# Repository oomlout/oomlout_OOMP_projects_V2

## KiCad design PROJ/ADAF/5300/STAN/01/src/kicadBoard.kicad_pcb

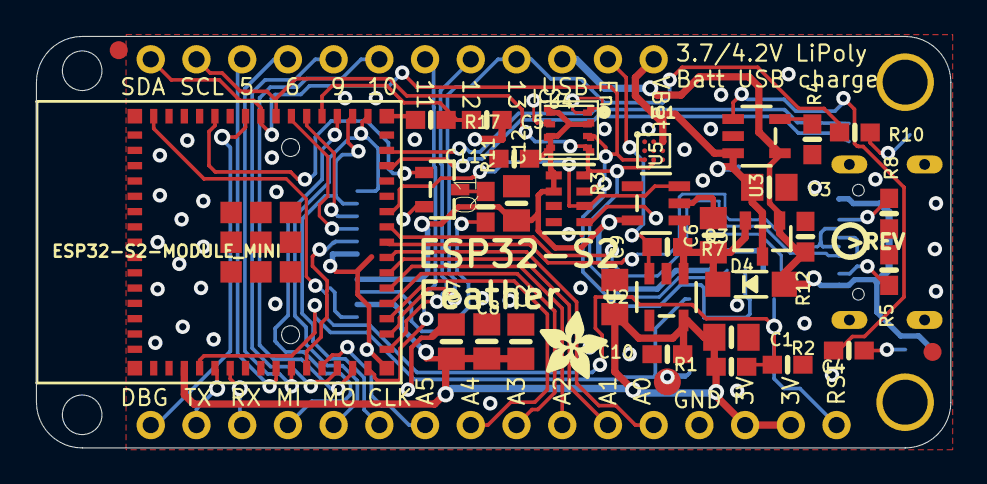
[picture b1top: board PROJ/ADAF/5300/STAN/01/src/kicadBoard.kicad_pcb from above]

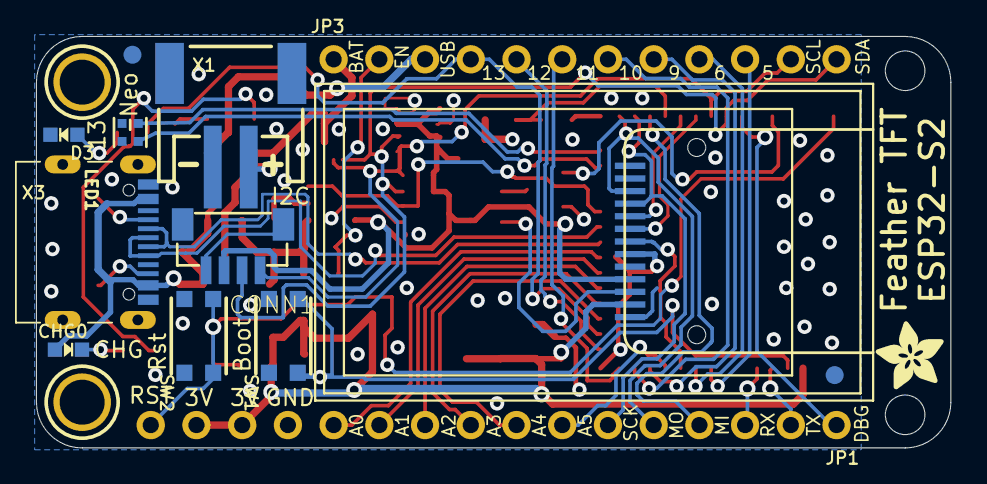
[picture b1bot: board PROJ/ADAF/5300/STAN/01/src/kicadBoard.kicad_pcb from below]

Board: 2 copper layers, 50.8 x 22.9 mm, 56 parts (16 on the bottom side), 48 nets.

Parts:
@HOLE0, @HOLE1: (no value)
C1, C2, C7, C9, C12: 10uF; 0805-NO
C3, C6, C8: 10µF; 0805-NO
C4, C5, C10, C11: 1uF; 0603-NO
CHG0: ORANGE; CHIPLED_0603_NOOUTLINE
CONN1: STEMMA_I2C_QTRA; JST_SH4_RA
D3: RED; CHIPLED_0603_NOOUTLINE
D4: MBR540; SOD-123
DISP1: DISP_LCD_GENERIC_SPI_1.14IN_240X135_WRAPUNDER; TFT_1.14IN_240X135_WRAPUNDER
IC1: LC709203F/MH; WLCSP9
IC2: BME680
JP1: 1X16_ROUND_MIN
JP3: 1X12_ROUND_MIN
LED1: WS2812B_SK6805_1515; SK6805_1515
Q1: BSS138; SOT23-R
Q3: DMG3415U; SOT23-R
R1, R2, R4, R5, R8, R10: 5.1K; 0603-NO
R3: 10K; RESPACK_4X0603
R7, R12: 100K; 0603-NO
R11: 22; 0603-NO
R17: 1Meg; 0603-NO
SW1, SW2: KMR2; BTN_KMR2_4.6X2.8
TP1: TESTPOINT_ROUND_1.5MM_NO
U1: ESP32-S2-MODULE_MINI; QFN60_ESP32-S2-MINI-1_EXP
U2, U5: AP2112-3.3; SOT23-5
U3: MCP73831T-2ACI/OT; SOT23-5
U4: BME280
U$7: PCBFEAT-REV-040
U$9, U$54: ADAFRUIT_3.5MM
U$31, U$32: MOUNTINGHOLE2.5; MOUNTINGHOLE_2.5_PLATED
U$34, U$35, U$55, U$56: FIDUCIAL_1MM
X1: JSTPH; JSTPH2_BATT
X3: USB C; USB_C_CUSB31-CFM2AX-01-X

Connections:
3.3V: C1.1, C2.1, C7.1, C8.1, C9.1, C10.1, DISP1.12, JP1.14, JP1.15, R1.2, U1.3, U2.5
A0: JP1.12, U1.22
A1: JP1.11, U1.21
A2: JP1.10, U1.20
A3: JP1.9, U1.19
A4: JP1.8, U1.18
A5: JP1.7, U1.12
BACKLITE: Q1.1, U1.41
BOOT0: SW1.B, SW1.B', TP1.P$1, U1.4
D5: JP3.10, U1.9
D6: JP3.9, U1.10
D9: JP3.8, U1.13
D10: JP3.7, U1.14
D11: JP3.6, U1.15
D12: JP3.5, U1.16
D13: JP3.4, R10.1, U1.17
D+: U1.24, X3.A6, X3.B6
D-: U1.23, X3.A7, X3.B7
EN: JP3.2, R7.1, U2.3
GND: C1.2, C2.2, C3.2, C4.2, C5.2, C6.2, C7.2, C8.2, C9.2, C10.2, C11.2, C12.2, CONN1.1, CONN1.MT1, CONN1.MT2, D3.C, DISP1.8, DISP1.13, IC1.A1, IC1.B1, IC2.1, IC2.7, JP1.13, LED1.4, Q1.2, R3.3, R3.4, R3.5, R4.1, R5.1, R8.1, R12.1, R17.1, SW1.A, SW1.A', SW2.A, SW2.A', U1.1, U1.2, U1.30, U1.42, U1.43, U1.46, U1.47, U1.48, U1.49, U1.50, U1.51, U1.52, U1.53, U1.54, U1.55, U1.56, U1.57, U1.58, U1.59, U1.60, U1.61, U1.62, U1.63, U1.64, U1.65, U1.66, U1.67, U1.68, U1.69, U1.70, U1.71, U1.72, U1.73, U2.2, U3.2, U4.1, U4.7, U5.2, X1.1, X1.NC1, X1.NC2, X3.A1B12, X3.B1A12
I2C_PWR: R3.6, U1.25, U5.3
IO38_DBLTAP: C5.1, R17.2, U1.34
LEDK: DISP1.11, R11.1
MISO: JP1.4, U1.33
MOSI: DISP1.3, JP1.5, U1.31
unnamed: CHG0.C, R2.1
unnamed: Q1.3, R11.2
unnamed: R2.2, U3.1
unnamed: R4.2, U3.5
unnamed: D3.A, R10.2
unnamed: R8.2, X3.A5
unnamed: R5.2, X3.B5
NEOPIX: LED1.1, U1.28
NEOPIX_PWR: LED1.2, U1.29
RESET: C4.1, JP1.16, R1.1, SW2.B, SW2.B', U1.45
RX: JP1.3, U1.6
SCK: DISP1.4, JP1.6, U1.32
SCL: CONN1.4, IC1.C2, IC2.4, JP3.11, R3.8, U1.37, U4.4
SDA: CONN1.3, IC1.C1, IC2.3, JP3.12, R3.7, U1.38, U4.3
TFT_CS: DISP1.7, U1.11
TFT_DC: DISP1.5, U1.35
TFT_RST: DISP1.6, U1.36
TX: JP1.2, U1.5
TXD0: JP1.1, U1.39
VBAT: C3.1, IC1.A3, JP3.1, Q3.3, U3.3, X1.2
VBUS: CHG0.A, D4.A, JP3.3, Q3.1, R12.2, U3.4, X3.A4B9, X3.B4A9
VHI: C6.1, D4.C, Q3.2, R7.2, U2.1, U5.1
VSENSOR: C11.1, C12.1, CONN1.2, DISP1.10, IC2.2, IC2.5, IC2.6, IC2.8, R3.1, R3.2, U4.2, U4.5, U4.6, U4.8, U5.5

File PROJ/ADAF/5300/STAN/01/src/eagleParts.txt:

Partlist

Exported from boardEagle.brd at 08/08/2022 07:50

EAGLE Version 9.6.2 Copyright (c) 1988-2020 Autodesk, Inc.

Assembly variant: 

Part     Value                                         Package                      Library              Position (inch)       Orientation

C1       10uF                                          0805-NO                      microbuilder         (1.52 0.242)          R0
C2       10uF                                          0805-NO                      microbuilder         (1.0595 0.2325)       R90
C3       10µF                                          0805-NO                      microbuilder         (1.603 0.57)          R0
C4       1uF                                           0603-NO                      microbuilder         (1.643 0.182)         R0
C5       1uF                                           0603-NO                      microbuilder         (0.985 0.7175)        R0
C6       10µF                                          0805-NO                      microbuilder         (1.4804252 0.46519685) R90
C7       10uF                                          0805-NO                      microbuilder         (0.9075 0.2325)       R90
C8       10µF                                          0805-NO                      microbuilder         (0.98490945 0.2328622) R90
C9       10uF                                          0805-NO                      microbuilder         (1.265 0.33)          R90
C10      1uF                                           0603-NO                      microbuilder         (1.38 0.205)          R180
C11      1uF                                           0603-NO                      microbuilder         (1.045 0.6325)        R180
C12      10uF                                          0805-NO                      microbuilder         (1.05 0.535)          R90
CHG      ORANGE                                        CHIPLED_0603_NOOUTLINE       microbuilder         (1.93 0.215)          MR270
CONN1    STEMMA_I2C_QTRA                               JST_SH4_RA                   microbuilder         (1.57 0.455)          MR180
D3       RED                                           CHIPLED_0603_NOOUTLINE       microbuilder         (1.94 0.685)          MR90
D4       MBR540                                        SOD-123                      microbuilder         (1.563 0.358)         R0
DISP1    DISP_LCD_GENERIC_SPI_1.14IN_240X135_WRAPUNDER TFT_1.14IN_240X135_WRAPUNDER adafruit_display     (0.17 0.45)           MR90
IC1      LC709203F/MH                                  WLCSP9                       adafruit_sensor      (1.35 0.65)           R0
IC2      BME680                                        BME680                       adafruit_sensor      (1.165 0.695)         R0
JP1                                                    1X16_ROUND_MIN               microbuilder         (1 0.05)              MR180
JP3                                                    1X12_ROUND_MIN               microbuilder         (0.8 0.85)            MR0
LED1     WS2812B_SK6805_1515                           SK6805_1515                  microbuilder         (1.795 0.69)          MR90
Q1       BSS138                                        SOT23-R                      microbuilder         (0.8875 0.565)        R270
Q3       DMG3415U                                      SOT23-R                      microbuilder         (1.588 0.458)         R180
R1       5.1K                                          0603-NO                      microbuilder         (1.52 0.1775)         R180
R2       5.1K                                          0603-NO                      microbuilder         (1.777 0.213)         R180
R3       10K                                           RESPACK_4X0603               microbuilder         (1.165 0.545)         R270
R4       5.1K                                          0603-NO                      microbuilder         (1.697 0.675)         R90
R5       5.1K                                          0603-NO                      microbuilder         (1.865 0.389)         R270
R7       100K                                          0603-NO                      microbuilder         (1.38 0.4395)         R0
R8       5.1K                                          0603-NO                      microbuilder         (1.865 0.5125)        R90
R10      5.1K                                          0603-NO                      microbuilder         (1.79 0.69)           R0
R11      22                                            0603-NO                      microbuilder         (0.9825 0.5275)       R90
R12      100K                                          0603-NO                      microbuilder         (1.682 0.462)         R270
R17      1Meg                                          0603-NO                      microbuilder         (0.8625 0.7175)       R0
SW1      KMR2                                          BTN_KMR2_4.6X2.8             microbuilder         (1.46 0.245)          MR90
SW2      KMR2                                          BTN_KMR2_4.6X2.8             microbuilder         (1.645 0.245)         MR90
TP1                                                    TESTPOINT_ROUND_1.5MM_NO     microbuilder         (1.38 0.1445)         R180
U$31     MOUNTINGHOLE2.5                               MOUNTINGHOLE_2.5_PLATED      microbuilder         (1.9 0.8)             MR270
U$32     MOUNTINGHOLE2.5                               MOUNTINGHOLE_2.5_PLATED      microbuilder         (1.9 0.1)             MR270
U$34     FIDUCIAL_1MM                                  FIDUCIAL_1MM                 microbuilder         (1.79 0.86)           MR270
U$35     FIDUCIAL_1MM                                  FIDUCIAL_1MM                 microbuilder         (0.25414173 0.15927559) MR270
U$55     FIDUCIAL_1MM                                  FIDUCIAL_1MM                 microbuilder         (1.96 0.21)           R0
U$56     FIDUCIAL_1MM                                  FIDUCIAL_1MM                 microbuilder         (0.18 0.87)           R0
U1       ESP32-S2-MODULE_MINI                          QFN60_ESP32-S2-MINI-1_EXP    adafruit_wireless    (0.4 0.45)            R90
U2       AP2112-3.3                                    SOT23-5                      microbuilder         (1.378 0.33)          R180
U3       MCP73831T-2ACI/OT                             SOT23-5                      microbuilder         (1.575 0.682)         R270
U4       BME280                                        BME280                       adafruit_sensor      (1.165 0.695)         R0
U5       AP2112-3.3                                    SOT23-5                      microbuilder         (1.355 0.535)         R90
X1       JSTPH                                         JSTPH2_BATT                  adafruit_electromech (1.575 0.76)          MR0
X3       USB C                                         USB_C_CUSB31-CFM2AX-01-X     adafruit_connector   (1.895 0.45)          MR270

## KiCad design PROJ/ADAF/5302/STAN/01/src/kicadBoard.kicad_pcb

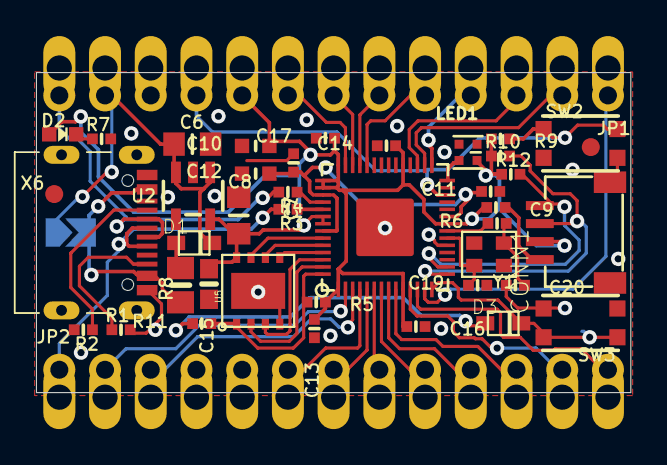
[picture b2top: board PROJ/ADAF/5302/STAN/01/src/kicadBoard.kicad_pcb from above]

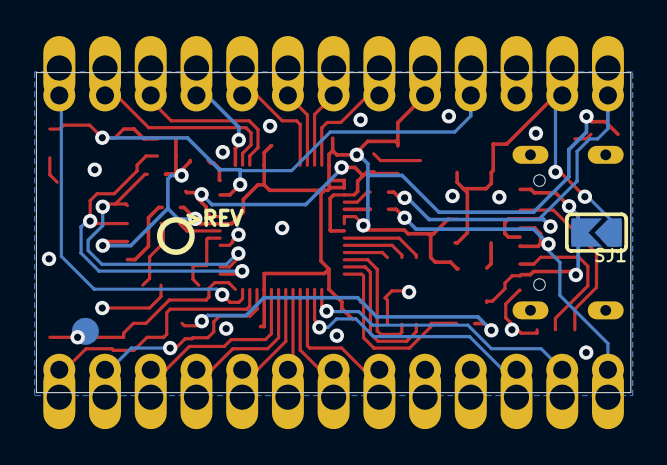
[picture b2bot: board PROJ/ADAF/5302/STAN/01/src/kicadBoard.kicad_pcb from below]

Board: 4 copper layers, 33.0 x 17.8 mm, 47 parts (4 on the bottom side), 46 nets.

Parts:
C6, C8: 10µF; _0805MP
C7, C9, C11, C13, C14, C16, C17: 0.1uF; _0402NO
C10, C12: 1uF; _0603MP
C15: 1uF; 0603-NO
C19, C20: 22pF; _0402NO
CONN1: STEMMA_I2C_QTSKINNY; JST_SH4_SKINNY
D1, D3: NSR0320; SOD-323F
D2: GREEN; CHIPLED_0603_NOOUTLINE
IC2: RP2040_QFN56; QFN56_7MM_REDUCEDEPAD
JP1, JP2: 1X13_CASTEL
LED1: WS2812B_SK6805_1515; SK6805_1515
R1, R2, R10, R12: 5.1K; _0402NO
R3, R4: 27; _0402NO
R5, R7, R9: 10K; _0402NO
R6, R11: 1K; _0402NO
R8: FUSE; 0805-NO
SJ1: SOLDERJUMPER_ARROW_NOPASTE
SW2, SW3: KMR2; BTN_KMR2_4.6X2.8
TP1: TESTPOINT_ROUND_1.5MM_NO
U2: AP2112K-3.3; SOT23-5
U5: 8MB QSPI Flash; USON8_4X4
U$17: KB2040_BOT
U$19: KB2040_TOP
U$20: PCBFEAT-REV-040
U$34, U$35: FIDUCIAL_1MM
X6: USB TYPE C; USB_C_CUSB31-CFM2AX-01-X
Y1: 12MHZ; CRYSTAL_2.5X2

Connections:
1.2V: C7.2, C11.2, C12.1, IC2.23, IC2.45, IC2.50
3.3V: C8.1, C9.1, C10.1, C13.1, C14.1, C15.1, C16.1, C17.1, CONN1.2, D2.A, IC2.1, IC2.10, IC2.22, IC2.33, IC2.42, IC2.43, IC2.44, IC2.48, IC2.49, JP1.9, JP1.9C, LED1.2, R5.2, R9.1, R10.1, R12.1, U2.5, U5.8
A0: IC2.38, JP1.5, JP1.5C
A1: IC2.39, JP1.6, JP1.6C
A2: IC2.40, JP1.7, JP1.7C
A3: IC2.41, JP1.8, JP1.8C
CC1: R2.1, X6.A5
CC2: R1.1, X6.B5
D0: IC2.2, JP2.2, JP2.2C
D1: IC2.3, JP2.3, JP2.3C
D2: IC2.4, JP2.6, JP2.6C
D3: IC2.5, JP2.7, JP2.7C
D4: IC2.6, JP2.8, JP2.8C
D5: IC2.7, JP2.9, JP2.9C
D6: IC2.8, JP2.10, JP2.10C
D7: IC2.9, JP2.11, JP2.11C
D8: IC2.11, JP2.12, JP2.12C
D9: IC2.12, JP2.13, JP2.13C
D10: IC2.13, JP1.1, JP1.1C
D+: JP2.1, JP2.1C, R3.2, X6.A6, X6.B6
D-: JP1.13, JP1.13C, R4.2, X6.A7, X6.B7
GND: C6.2, C7.1, C8.2, C9.2, C10.2, C11.1, C12.2, C13.2, C14.2, C15.2, C16.2, C17.2, C19.1, C20.1, CONN1.1, CONN1.MT1, CONN1.MT2, IC2.19, IC2.P$1, JP1.11, JP1.11C, JP2.4, JP2.4C, JP2.5, JP2.5C, LED1.4, R1.2, R2.2, R7.2, SW2.B, SW2.B', SW3.B, SW3.B', U2.2, U5.4, U5.PAD, X6.A1B12, X6.B1A12
MISO: IC2.31, JP1.3, JP1.3C
MOSI: IC2.30, JP1.2, JP1.2C
unnamed: IC2.47, R3.1
unnamed: D2.C, R7.1
unnamed: IC2.46, R4.1
unnamed: D3.A, R11.2
unnamed: C19.2, IC2.20, Y1.3
unnamed: C20.2, R6.1, Y1.1
unnamed: IC2.21, R6.2
unnamed: D1.A, R8.2
NEOPIX: IC2.28, LED1.1
QSPI_CS: IC2.56, R5.1, R11.1, U5.1
QSPI_DATA[0]: IC2.53, U5.5
QSPI_DATA[1]: IC2.55, U5.2
QSPI_DATA[2]: IC2.54, U5.3
QSPI_DATA[3]: IC2.51, U5.7
QSPI_SCK: IC2.52, U5.6
RAW: C6.1, D1.C, JP1.12, JP1.12C, SJ1.1, U2.1, U2.3
SCL: CONN1.4, IC2.16, R12.2
SCLK: IC2.29, JP1.4, JP1.4C
SDA: CONN1.3, IC2.15, R10.2
USBBOOT: D3.C, IC2.14, SW3.A, SW3.A', TP1.P$1
VBUS: R8.1, SJ1.2, X6.A4B9, X6.B4A9
~RESET: IC2.26, JP1.10, JP1.10C, R9.2, SW2.A, SW2.A'

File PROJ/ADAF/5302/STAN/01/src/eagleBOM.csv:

"Part";"Value";"Device";"Package";"Description";"BOM";"REV";
"C6";"10µF";"CAP_CERAMIC_0805MP";"_0805MP";"Ceramic Capacitors";"";"";
"C7";"0.1uF";"CAP_CERAMIC_0402NO";"_0402NO";"Ceramic Capacitors";"";"";
"C8";"10µF";"CAP_CERAMIC_0805MP";"_0805MP";"Ceramic Capacitors";"";"B";
"C9";"0.1uF";"CAP_CERAMIC_0402NO";"_0402NO";"Ceramic Capacitors";"";"";
"C10";"1uF";"CAP_CERAMIC_0603MP";"_0603MP";"Ceramic Capacitors";"";"";
"C11";"0.1uF";"CAP_CERAMIC_0402NO";"_0402NO";"Ceramic Capacitors";"";"";
"C12";"1uF";"CAP_CERAMIC_0603MP";"_0603MP";"Ceramic Capacitors";"";"";
"C13";"0.1uF";"CAP_CERAMIC_0402NO";"_0402NO";"Ceramic Capacitors";"";"";
"C14";"0.1uF";"CAP_CERAMIC_0402NO";"_0402NO";"Ceramic Capacitors";"";"";
"C15";"1uF";"CAP_CERAMIC0603_NO";"0603-NO";"Ceramic Capacitors";"";"";
"C16";"0.1uF";"CAP_CERAMIC_0402NO";"_0402NO";"Ceramic Capacitors";"";"";
"C17";"0.1uF";"CAP_CERAMIC_0402NO";"_0402NO";"Ceramic Capacitors";"";"";
"C19";"22pF";"CAP_CERAMIC_0402NO";"_0402NO";"Ceramic Capacitors";"";"";
"C20";"22pF";"CAP_CERAMIC_0402NO";"_0402NO";"Ceramic Capacitors";"";"";
"CONN1";"STEMMA_I2C_QTSKINNY";"STEMMA_I2C_QTSKINNY";"JST_SH4_SKINNY";"";"";"";
"D1";"NSR0320";"DIODESOD-323F";"SOD-323F";"Diode";"";"";
"D2";"GREEN";"LED0603_NOOUTLINE";"CHIPLED_0603_NOOUTLINE";"LED";"";"";
"D3";"NSR0320";"DIODESOD-323F";"SOD-323F";"Diode";"";"";
"IC2";"RP2040_QFN56";"RP2040_QFN56";"QFN56_7MM_REDUCEDEPAD";"";"";"";
"JP1";"";"HEADER-1X13_CASTEL";"1X13_CASTEL";"";"";"";
"JP2";"";"HEADER-1X13_CASTEL";"1X13_CASTEL";"";"";"";
"LED1";"WS2812B_SK6805_1515";"WS2812B_SK6805_1515";"SK6805_1515";"";"";"";
"R1";"5.1K";"RESISTOR_0402NO";"_0402NO";"Resistors";"";"";
"R2";"5.1K";"RESISTOR_0402NO";"_0402NO";"Resistors";"";"";
"R3";"27";"RESISTOR_0402NO";"_0402NO";"Resistors";"";"";
"R4";"27";"RESISTOR_0402NO";"_0402NO";"Resistors";"";"";
"R5";"10K";"RESISTOR_0402NO";"_0402NO";"Resistors";"";"";
"R6";"1K";"RESISTOR_0402NO";"_0402NO";"Resistors";"";"";
"R7";"10K";"RESISTOR_0402NO";"_0402NO";"Resistors";"";"";
"R8";"FUSE";"RESISTOR0805_NOOUTLINE";"0805-NO";"Resistors";"";"";
"R9";"10K";"RESISTOR_0402NO";"_0402NO";"Resistors";"";"";
"R10";"5.1K";"RESISTOR_0402NO";"_0402NO";"Resistors";"";"";
"R11";"1K";"RESISTOR_0402NO";"_0402NO";"Resistors";"";"";
"R12";"5.1K";"RESISTOR_0402NO";"_0402NO";"Resistors";"";"";
"SJ1";"";"SOLDERJUMPER";"SOLDERJUMPER_ARROW_NOPASTE";"SMD Solder JUMPER";"EXCLUDE";"";
"SW2";"KMR2";"SWITCH_TACT_SMT4.6X2.8";"BTN_KMR2_4.6X2.8";"SMT Tact Switches";"";"";
"SW3";"KMR2";"SWITCH_TACT_SMT4.6X2.8";"BTN_KMR2_4.6X2.8";"SMT Tact Switches";"";"";
"TP1";"";"TESTPOINTROUND1.5MMNO";"TESTPOINT_ROUND_1.5MM_NO";"Test Point";"";"";
"U$34";"FIDUCIAL_1MM";"FIDUCIAL_1MM";"FIDUCIAL_1MM";"Fiducial Alignment Points";"EXCLUDE";"";
"U$35";"FIDUCIAL_1MM";"FIDUCIAL_1MM";"FIDUCIAL_1MM";"Fiducial Alignment Points";"EXCLUDE";"";
"U2";"AP2112K-3.3";"VREG_SOT23-5";"SOT23-5";"SOT23-5 Fixed Voltage Regulators";"";"";
"U5";"8MB QSPI Flash";"SPIFLASH_8PIN_4X4";"USON8_4X4";"SOIC8 SPI Flash";"";"";
"X6";"USB TYPE C";"USB_C";"USB_C_CUSB31-CFM2AX-01-X";"USB Type-C USB 2.0 Connector";"";"";
"Y1";"12MHZ";"CRYSTAL2.5X2.0";"CRYSTAL_2.5X2";"Crystals";"";"";

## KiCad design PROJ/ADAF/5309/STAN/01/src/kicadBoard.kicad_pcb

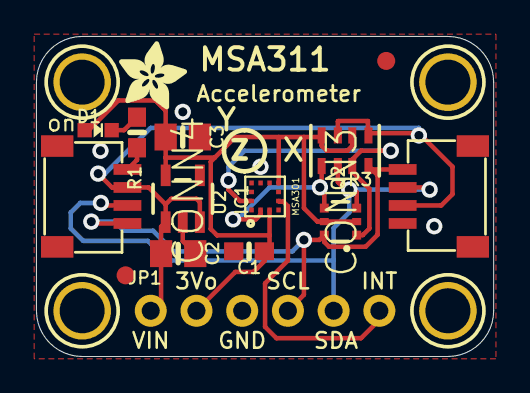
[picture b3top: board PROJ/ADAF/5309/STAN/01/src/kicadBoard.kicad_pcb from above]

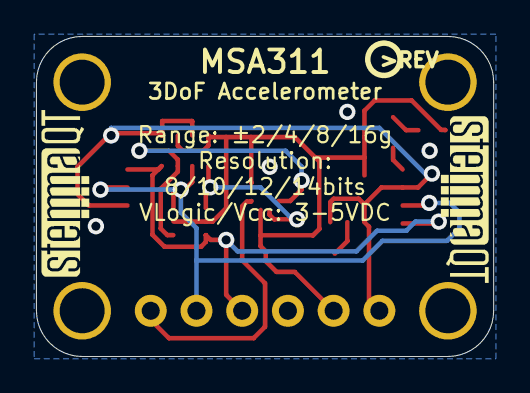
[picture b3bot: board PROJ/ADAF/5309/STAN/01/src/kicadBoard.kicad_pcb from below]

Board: 2 copper layers, 25.4 x 17.8 mm, 22 parts (3 on the bottom side), 9 nets.

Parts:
C1: 0.1uF; 0603-NO
C2, C3: 10uF; 0805-NO
CONN3, CONN4: STEMMA_I2C_QT; JST_SH4
D1: GREEN; CHIPLED_0603_NOOUTLINE
FID3, FID4: FIDUCIAL_1MM
IC1: MSA301; LGA12_2X2MM
JP1: 1X06_ROUND_70
Q2: BSS138; SOT363
R1: 4.7K; 0603-NO
R3: 10K; RESPACK_4X0603
U2: AP2112K-3.3; SOT23-5
U$1, U$17, U$19, U$21: MOUNTINGHOLE2.5; MOUNTINGHOLE_2.5_PLATED
U$22: ADAFRUIT_3.5MM
U$25: PCBFEAT-REV-040
U$30, U$31: STEMMAQT

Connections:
3.3V: C1.1, C3.1, D1.A, IC1.3, IC1.7, JP1.2, Q2.2, Q2.5, R3.2, R3.4, U2.5
GND: C1.2, C2.2, C3.2, CONN3.1, CONN4.1, IC1.9, JP1.3, R1.2, U2.2
INT: IC1.5, JP1.6
unnamed: D1.C, R1.1
SCL: CONN3.4, CONN4.4, JP1.4, Q2.6, R3.8
SCL_3V: IC1.12, Q2.1, R3.7
SDA: CONN3.3, CONN4.3, JP1.5, Q2.3, R3.6
SDA_3V: IC1.2, Q2.4, R3.5
VCC: C2.1, CONN3.2, CONN4.2, JP1.1, R3.1, R3.3, U2.1, U2.3

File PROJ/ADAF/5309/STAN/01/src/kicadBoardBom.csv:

"Id";"Designator";"Package";"Quantity";"Designation";"Supplier and ref";
1;"U$22";"ADAFRUIT_3.5MM";1;"";;;
2;"U$21,U$17,U$19,U$1";"MOUNTINGHOLE_2.5_PLATED";4;"MOUNTINGHOLE2.5";;;
3;"FID4,FID3";"FIDUCIAL_1MM";2;"FIDUCIAL_1MM";;;
4;"JP1";"1X06_ROUND_70";1;"";;;
5;"CONN4,CONN3";"JST_SH4";2;"STEMMA_I2C_QT";;;
6;"U2";"SOT23-5";1;"AP2112K-3.3";;;
7;"IC1";"LGA12_2X2MM";1;"MSA301";;;
8;"C1";"0603-NO";1;"0.1uF";;;
9;"R1";"0603-NO";1;"4.7K";;;
10;"Q2";"SOT363";1;"BSS138";;;
11;"C2,C3";"0805-NO";2;"10uF";;;
12;"R3";"RESPACK_4X0603";1;"10K";;;
13;"D1";"CHIPLED_0603_NOOUTLINE";1;"GREEN";;;
14;"U$31,U$30";"STEMMAQT";2;"";;;
15;"U$25";"PCBFEAT-REV-040";1;"";;;

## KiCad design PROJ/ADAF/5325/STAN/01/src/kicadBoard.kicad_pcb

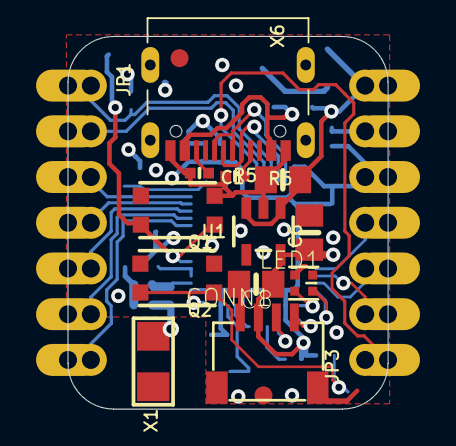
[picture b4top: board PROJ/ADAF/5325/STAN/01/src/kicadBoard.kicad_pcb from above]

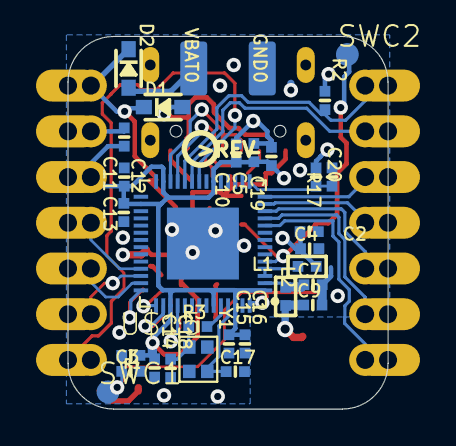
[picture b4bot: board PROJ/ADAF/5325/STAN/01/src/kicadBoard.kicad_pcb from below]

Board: 4 copper layers, 17.8 x 20.7 mm, 50 parts (33 on the bottom side), 33 nets.

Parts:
C1, C6, C8: 22uF; 0805-NO
C2, C3, C5, C13, C15, C19, C20: 1uF; _0402NO
C4, C10, C11, C12, C14: 0.1uF; _0402NO
C7, C9: TBD; _0402NO
C16: 100pF; _0402NO
C17, C18: 16pF; _0402NO
CONN1: STEMMA_I2C_QTSKINNY; JST_SH4_SKINNY
D1, D2: NSR0320; SOD-323_MINI
GND0: TESTPOINT_RECT_1X3MM
JP1, JP3: 1X07_CASTEL
L1: 2nH; _0402
L2: 0 ohm; _0402
LED1: WS2812B_SK6805_1515; SK6805_1515
Q1: BOOT0; BTN_KMR2_4.6X2.8
Q2: reset; BTN_KMR2_4.6X2.8
R1, R2: 10K; _0402NO
R3: 0; _0402NO
R5, R6: 5.1K; _0402NO
R17: 1Meg; _0402NO
SWC1, SWC2: TPB1,27; B1,27
U1: AP2112K-3.3; SOT23-5
U$3: QTPYS2_TOP
U$6, U$8: FIDUCIAL_1MM
U$7: QTPYS2_BOT
U$12: PCBFEAT-REV-040
U$15: ESP32-S2QFN54; QFN40P700X700X90-57T400N
VBAT0: TESTPOINT_RECT_1X3MM
X1: ANT_2450AT18B100
X6: USB TYPE C; USB_C_CUSB31-CFM2AX-01-X
Y1: 40MHz; CRYSTAL_2X1.6

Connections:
3.3V: C2.1, C4.1, C5.1, C6.1, C8.1, C10.1, C11.1, C12.1, C13.1, C14.1, C15.1, C16.1, C19.1, CONN1.2, JP3.5, JP3.5C, L1.1, R1.1, R2.1, U1.5, U$15.1, U$15.20, U$15.27, U$15.30, U$15.45, U$15.51, U$15.54
+5V: C1.1, D1.C, D2.C, JP3.7, JP3.7C, U1.1, U1.3
A0: JP1.1, JP1.1C, R2.2, U$15.24
A1: JP1.2, JP1.2C, U$15.23
A2: JP1.3, JP1.3C, U$15.14
A3: JP1.4, JP1.4C, U$15.13
CC1: R6.2, X6.A5
CC2: R5.2, X6.B5
D+: U$15.26, X6.A6, X6.B6
D-: U$15.25, X6.A7, X6.B7
GND: C1.2, C2.2, C3.2, C4.2, C5.2, C6.2, C7.2, C8.2, C9.2, C10.2, C11.2, C12.2, C13.2, C14.2, C15.2, C16.2, C17.2, C18.2, C19.2, C20.2, CONN1.1, CONN1.MT1, CONN1.MT2, GND0.P$1, JP3.6, JP3.6C, LED1.4, Q1.B, Q1.B', Q2.B, Q2.B', R5.1, R6.1, R17.1, U1.2, U$15.57, X6.A1B12, X6.B1A12
IO0: Q1.A, Q1.A', SWC2.TP, U$15.5
IO10_DBLTAP: C20.1, R17.2, U$15.15
MISO: JP3.3, JP3.3C, U$15.41
MOSI: JP3.4, JP3.4C, U$15.39
unnamed: C7.1, L2.2, U$15.2
unnamed: C9.1, L2.1, X1.FP
unnamed: R3.2, U$15.52
unnamed: C17.1, U$15.53, Y1.3
unnamed: C18.1, R3.1, Y1.1
NEOPIX: LED1.1, U$15.43
NEOPIX_PWR: LED1.2, U$15.42
RX: JP3.1, JP3.1C, U$15.22
SCK: JP3.2, JP3.2C, U$15.40
SCL: JP1.6, JP1.6C, U$15.11
SCL1: CONN1.4, U$15.44
SDA: JP1.5, JP1.5C, U$15.12
SDA1: CONN1.3, U$15.46
TX: JP1.7, JP1.7C, U$15.10
VBAT: D2.A, VBAT0.P$1
VBUS: D1.A, X6.A4B9, X6.B4A9
VDD3P3: L1.2, U$15.3, U$15.4
~RESET: C3.1, Q2.A, Q2.A', R1.2, SWC1.TP, U$15.56

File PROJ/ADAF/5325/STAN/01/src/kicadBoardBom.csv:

"Id";"Designator";"Package";"Quantity";"Designation";"Supplier and ref";
1;"R6,R5";"_0402NO";2;"5.1K";;;
2;"JP1,JP3";"1X07_CASTEL";2;"";;;
3;"X1";"ANT_2450AT18B100";1;"";;;
4;"X6";"USB_C_CUSB31-CFM2AX-01-X";1;"USB TYPE C";;;
5;"U$6,U$8";"FIDUCIAL_1MM";2;"FIDUCIAL_1MM";;;
6;"CONN1";"JST_SH4_SKINNY";1;"STEMMA_I2C_QTSKINNY";;;
7;"U$3";"QTPYS2_TOP";1;"";;;
8;"C6,C8,C1";"0805-NO";3;"22uF";;;
9;"U1";"SOT23-5";1;"AP2112K-3.3";;;
10;"LED1";"SK6805_1515";1;"WS2812B_SK6805_1515";;;
11;"Q2";"BTN_KMR2_4.6X2.8";1;"reset";;;
12;"Q1";"BTN_KMR2_4.6X2.8";1;"BOOT0";;;
13;"C18,C17";"_0402NO";2;"16pF";;;
14;"U$7";"QTPYS2_BOT";1;"";;;
15;"R17";"_0402NO";1;"1Meg";;;
16;"C14,C12,C10,C11,C4";"_0402NO";5;"0.1uF";;;
17;"R2,R1";"_0402NO";2;"10K";;;
18;"C15,C2,C20,C19,C3,C13,C5";"_0402NO";7;"1uF";;;
19;"SWC2,SWC1";"B1,27";2;"TPB1,27";;;
20;"C7,C9";"_0402NO";2;"TBD";;;
21;"L2";"_0402";1;"0 ohm";;;
22;"C16";"_0402NO";1;"100pF";;;
23;"VBAT0,GND0";"TESTPOINT_RECT_1X3MM";2;"";;;
24;"R3";"_0402NO";1;"0";;;
25;"L1";"_0402";1;"2nH";;;
26;"U$15";"QFN40P700X700X90-57T400N";1;"ESP32-S2QFN54";;;
27;"U$12";"PCBFEAT-REV-040";1;"";;;
28;"Y1";"CRYSTAL_2X1.6";1;"40MHz";;;
29;"D1,D2";"SOD-323_MINI";2;"  NSR0320";;;

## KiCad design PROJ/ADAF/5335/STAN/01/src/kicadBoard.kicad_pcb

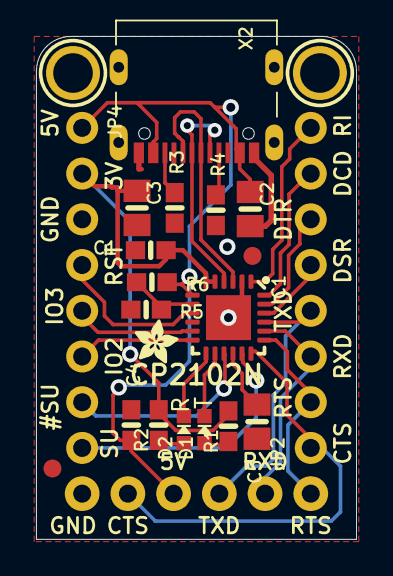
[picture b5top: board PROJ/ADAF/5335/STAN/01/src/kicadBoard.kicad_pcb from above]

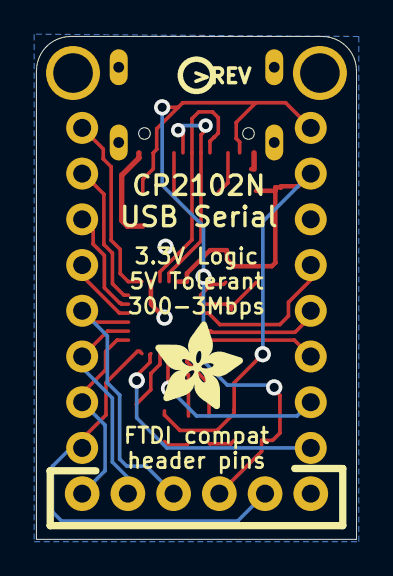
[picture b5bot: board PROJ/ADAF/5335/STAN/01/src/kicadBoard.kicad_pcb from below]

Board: 2 copper layers, 17.8 x 27.9 mm, 25 parts (2 on the bottom side), 26 nets.

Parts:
C1, C4: 0.1uF; 0603-NO
C2, C3, C5: 10uF; 0805-NO
D1: RED; CHIPLED_0603_NOOUTLINE
D2: GREEN; CHIPLED_0603_NOOUTLINE
FID1, FID2: FIDUCIAL_1MM
IC1: CP2102N-24; QFN24_4MM_SMSC
JP1: FTDI; 1X06_ROUND_76
JP2: Modem; 1X08_ROUND_70
JP4: Control; 1X08_ROUND_70
R1, R2, R6: 20K; 0603-NO
R3, R4: 5.1K; 0603-NO
R5: 47K; 0603-NO
U$8: ADAFRUIT_2.5MM
U$17: PCBFEAT-REV-040
U$18, U$19: MOUNTINGHOLE2.0; MOUNTINGHOLE_2.0_PLATED
U$22: ADAFRUIT_5MM
X2: USB_C_CUSB31-CFM2AX-01-X

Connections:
3.3V: C1.1, C3.1, IC1.5, IC1.6, JP4.2, R1.2, R2.2
#SUSP: IC1.15, JP4.7
CC1: R4.2, X2.A5
CC2: R3.2, X2.B5
CTS: IC1.18, JP1.2, JP2.1
D+: IC1.3, X2.A6, X2.B6
D-: IC1.4, X2.A7, X2.B7
DCD: IC1.24, JP2.7
DSR: IC1.22, JP2.5
DTR: IC1.23, JP2.6
GND: C1.2, C2.2, C3.2, C4.2, C5.2, IC1.2, IC1.THERM, JP1.1, JP4.3, R3.1, R4.1, R5.1, X2.A1B12, X2.B1A12
GPIO2: IC1.12, JP4.6
GPIO3: IC1.11, JP4.5
unnamed: D1.A, R1.1
unnamed: C5.1, IC1.16
unnamed: D2.A, R2.1
unnamed: D1.C, IC1.14
unnamed: D2.C, IC1.13
RI: IC1.1, JP2.8
RST: IC1.9, JP4.4
RTS: IC1.19, JP1.6, JP2.2
RXD: IC1.20, JP1.5, JP2.3
SUSP: IC1.17, JP4.8
TXD: IC1.21, JP1.4, JP2.4
VBUS: C2.1, C4.1, IC1.7, JP1.3, JP4.1, R6.2, X2.A4B9, X2.B4A9
VBUS_DETECT: IC1.8, R5.2, R6.1

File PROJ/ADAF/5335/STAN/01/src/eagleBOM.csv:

"Part";"Value";"Device";"Package";"Description";"BOM";
"C1";"0.1uF";"CAP_CERAMIC0603_NO";"0603-NO";"Ceramic Capacitors";"";
"C2";"10uF";"CAP_CERAMIC0805-NOOUTLINE";"0805-NO";"Ceramic Capacitors";"";
"C3";"10uF";"CAP_CERAMIC0805-NOOUTLINE";"0805-NO";"Ceramic Capacitors";"";
"C4";"0.1uF";"CAP_CERAMIC0603_NO";"0603-NO";"Ceramic Capacitors";"";
"C5";"10uF";"CAP_CERAMIC0805-NOOUTLINE";"0805-NO";"Ceramic Capacitors";"";
"D1";"RED";"LED0603_NOOUTLINE";"CHIPLED_0603_NOOUTLINE";"LED";"";
"D2";"GREEN";"LED0603_NOOUTLINE";"CHIPLED_0603_NOOUTLINE";"LED";"";
"FID1";"FIDUCIAL_1MM";"FIDUCIAL_1MM";"FIDUCIAL_1MM";"Fiducial Alignment Points";"EXCLUDE";
"FID2";"FIDUCIAL_1MM";"FIDUCIAL_1MM";"FIDUCIAL_1MM";"Fiducial Alignment Points";"EXCLUDE";
"IC1";"CP2102N-24";"CP2102N-24";"QFN24_4MM_SMSC";"";"";
"JP1";"FTDI";"HEADER-1X676MIL";"1X06_ROUND_76";"PIN HEADER";"";
"JP2";"Modem";"HEADER-1X870MIL";"1X08_ROUND_70";"PIN HEADER";"";
"JP4";"Control";"HEADER-1X870MIL";"1X08_ROUND_70";"PIN HEADER";"";
"R1";"20K";"RESISTOR_0603_NOOUT";"0603-NO";"Resistors";"";
"R2";"20K";"RESISTOR_0603_NOOUT";"0603-NO";"Resistors";"";
"R3";"5.1K";"RESISTOR_0603_NOOUT";"0603-NO";"Resistors";"";
"R4";"5.1K";"RESISTOR_0603_NOOUT";"0603-NO";"Resistors";"";
"R5";"47K";"RESISTOR_0603_NOOUT";"0603-NO";"Resistors";"";
"R6";"20K";"RESISTOR_0603_NOOUT";"0603-NO";"Resistors";"";
"U$18";"MOUNTINGHOLE2.0";"MOUNTINGHOLE2.0";"MOUNTINGHOLE_2.0_PLATED";"Mounting Hole";"EXCLUDE";
"U$19";"MOUNTINGHOLE2.0";"MOUNTINGHOLE2.0";"MOUNTINGHOLE_2.0_PLATED";"Mounting Hole";"EXCLUDE";
"X2";"";"USB_C";"USB_C_CUSB31-CFM2AX-01-X";"USB Type-C USB 2.0 Connector";"";

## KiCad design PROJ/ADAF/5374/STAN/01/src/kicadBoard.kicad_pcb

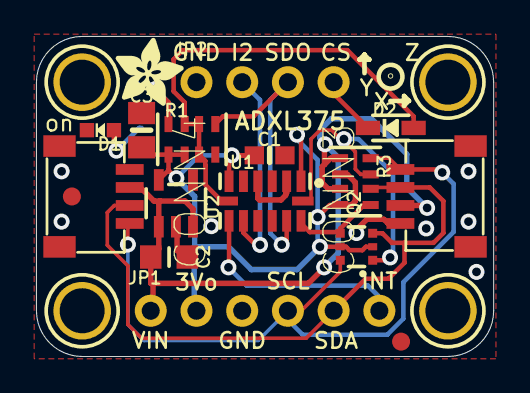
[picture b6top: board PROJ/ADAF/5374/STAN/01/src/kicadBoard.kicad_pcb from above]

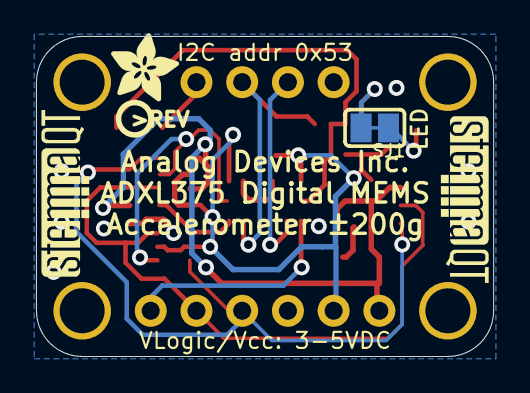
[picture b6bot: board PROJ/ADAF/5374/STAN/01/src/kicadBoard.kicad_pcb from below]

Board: 2 copper layers, 25.4 x 17.8 mm, 26 parts (5 on the bottom side), 14 nets.

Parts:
C1: 0.1uF; 0603-NO
C2: 10uF; _0805MP
C3: 10uF; 0805-NO
CONN3, CONN4: STEMMA_I2C_QT; JST_SH4
D1: GREEN; CHIPLED_0603_NOOUTLINE
D2: 1N4148; SOD-323
FID3, FID4: FIDUCIAL_1MM
JP1: 1X06_ROUND_70
JP2: 1X04_ROUND
Q2: BSS138; SOT363
R1, R3: 10K; RESPACK_4X0603
SJ1: SOLDERJUMPER_CLOSEDWIRE
U1: ADXL343; LGA14
U2: AP2112K-3.3; SOT23-5
U$1, U$17, U$19, U$21: MOUNTINGHOLE2.5; MOUNTINGHOLE_2.5_PLATED
U$4, U$11: ADAFRUIT_3.5MM
U$25: PCBFEAT-REV-040
U$30, U$31: STEMMAQT

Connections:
3.3V: C1.1, C3.1, JP1.2, Q2.2, Q2.5, R1.1, R1.2, R3.2, R3.4, U1.1, U1.6, U2.5
CS: D2.C, JP2.4
CS_3V: D2.A, R1.3, R1.6, R1.7, U1.7
GND: C1.2, C2.2, C3.2, CONN3.1, CONN3.MT1, CONN3.MT2, CONN4.1, CONN4.MT1, CONN4.MT2, D1.C, JP1.3, JP2.1, R1.4, U1.2, U1.4, U1.5, U2.2
INT1: JP1.6, U1.8
INT2: JP2.2, U1.9
unnamed: R1.8, SJ1.2
unnamed: D1.A, SJ1.1
SCL: CONN3.4, CONN4.4, JP1.4, Q2.6, R3.8
SCL_3V: Q2.1, R3.7, U1.14
SDA/SDIO: CONN3.3, CONN4.3, JP1.5, Q2.3, R3.6
SDA/SDIO_3V: Q2.4, R3.5, U1.13
SDO: JP2.3, R1.5, U1.12
VCC: C2.1, CONN3.2, CONN4.2, JP1.1, R3.1, R3.3, U2.1, U2.3

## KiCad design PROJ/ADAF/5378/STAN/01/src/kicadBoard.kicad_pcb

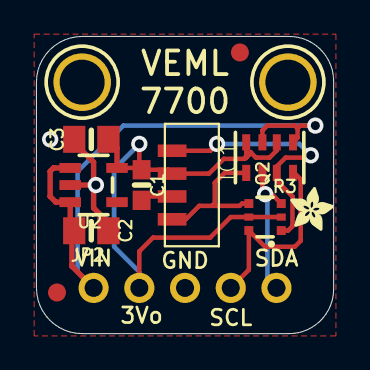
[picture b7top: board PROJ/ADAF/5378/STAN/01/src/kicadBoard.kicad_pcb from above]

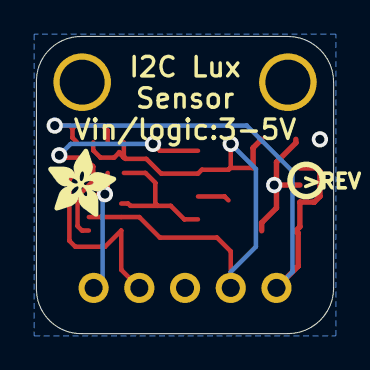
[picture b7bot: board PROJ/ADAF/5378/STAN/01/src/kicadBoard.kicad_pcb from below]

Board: 2 copper layers, 16.5 x 16.5 mm, 16 parts (3 on the bottom side), 7 nets.

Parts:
C1: 0.1uF; 0603-NO
C2, C3: 10uF; 0805-NO
FID1, FID2: FIDUCIAL_1MM
IC1: VEML7700
JP2: 1X05_ROUND
Q2: BSS138; SOT363
R3: 10K; RESPACK_4X0603
U2: AP2112K-3.3; SOT23-5
U$1: ADAFRUIT_3.5MM
U$3, U$4: MOUNTINGHOLE2.5; MOUNTINGHOLE_2.5_PLATED
U$8: ADAFRUIT_2.5MM
U$12: KATTNI_STOP
U$27: PCBFEAT-REV-040

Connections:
3.3V: C1.1, C3.1, IC1.2, JP2.2, Q2.2, Q2.5, R3.2, R3.4, U2.5
GND: C1.2, C2.2, C3.2, IC1.3, JP2.3, U2.2
SCL: JP2.4, Q2.6, R3.8
SCL_3V: IC1.1, Q2.1, R3.7
SDA: JP2.5, Q2.3, R3.6
SDA_3V: IC1.4, Q2.4, R3.5
VIN: C2.1, JP2.1, R3.1, R3.3, U2.1, U2.3
